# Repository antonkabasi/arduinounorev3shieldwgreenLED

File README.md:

# arduinounorev3shieldwgreenLED
KiCAD Arduino Uno Rev 3 Blank shield template with pin headers, mounting holes net connections, and green LED circuit connected to the arduino PWM output 10.

Pin header connections are labeled as nets connected to their corresponding Arduino pins.

To use the template:

1. File\Open project
2. Open schematic editor
3. Add your own components and connect them to corresponding nets in the Schematic Editor
4. Assemble your PCB using the PCB editor

To learn more check "How to Make Custom Arduino Shield in 2 Hours | Full Tutorial" by Robert Feranec on Youtube.

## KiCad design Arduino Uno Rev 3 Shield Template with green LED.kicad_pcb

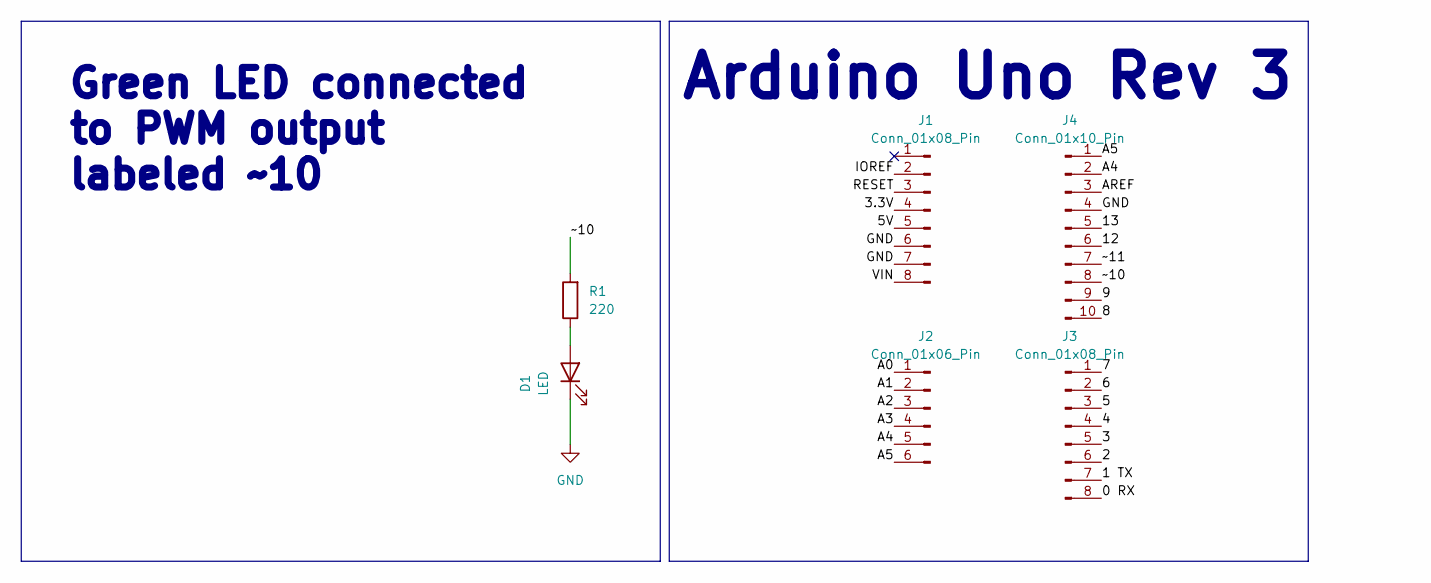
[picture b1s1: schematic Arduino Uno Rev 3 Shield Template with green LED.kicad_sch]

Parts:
D1: LED; LED_VCCLite_5381H5_6.35x6.35mm
J1, J3: Conn_01x08_Pin; PinSocket_1x08_P2.54mm_Vertical
J2: Conn_01x06_Pin; PinSocket_1x06_P2.54mm_Vertical
J4: Conn_01x10_Pin; PinSocket_1x10_P2.54mm_Vertical
R1: 220; R_Axial_DIN0207_L6.3mm_D2.5mm_P5.08mm_Vertical

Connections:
/0 RX: J3.8
/1 TX: J3.7
/2: J3.6
/3: J3.5
/3.3V: J1.4
/4: J3.4
/5: J3.3
/5V: J1.5
/6: J3.2
/7: J3.1
/8: J4.10
/9: J4.9
/12: J4.6
/13: J4.5
/A0: J2.1
/A1: J2.2
/A2: J2.3
/A3: J2.4
/A4: J2.5, J4.2
/A5: J2.6, J4.1
/AREF: J4.3
/IOREF: J1.2
/RESET: J1.3
/VIN: J1.8
/~10: J4.8, R1.2
/~11: J4.7
GND: D1.1 (K), J1.6, J1.7, J4.4
unnamed: D1.2 (A), R1.1

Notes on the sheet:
Green LED connected to PWM output labeled ~10
Arduino Uno Rev 3

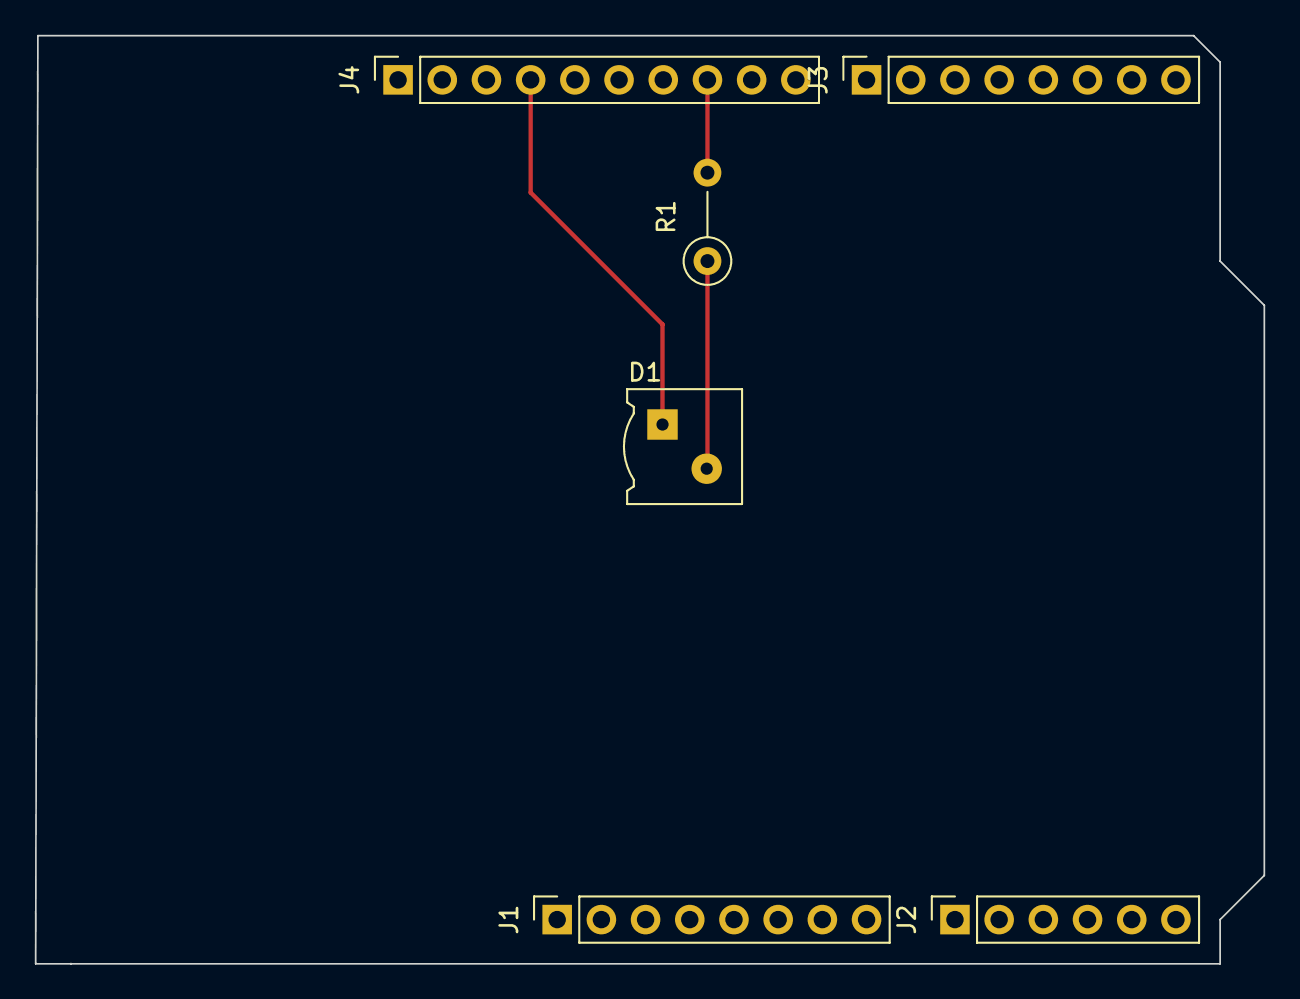
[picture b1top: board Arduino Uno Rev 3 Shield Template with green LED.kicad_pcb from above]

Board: 2 copper layers, 70.6 x 53.3 mm, 6 parts (0 on the bottom side), 5 nets.
